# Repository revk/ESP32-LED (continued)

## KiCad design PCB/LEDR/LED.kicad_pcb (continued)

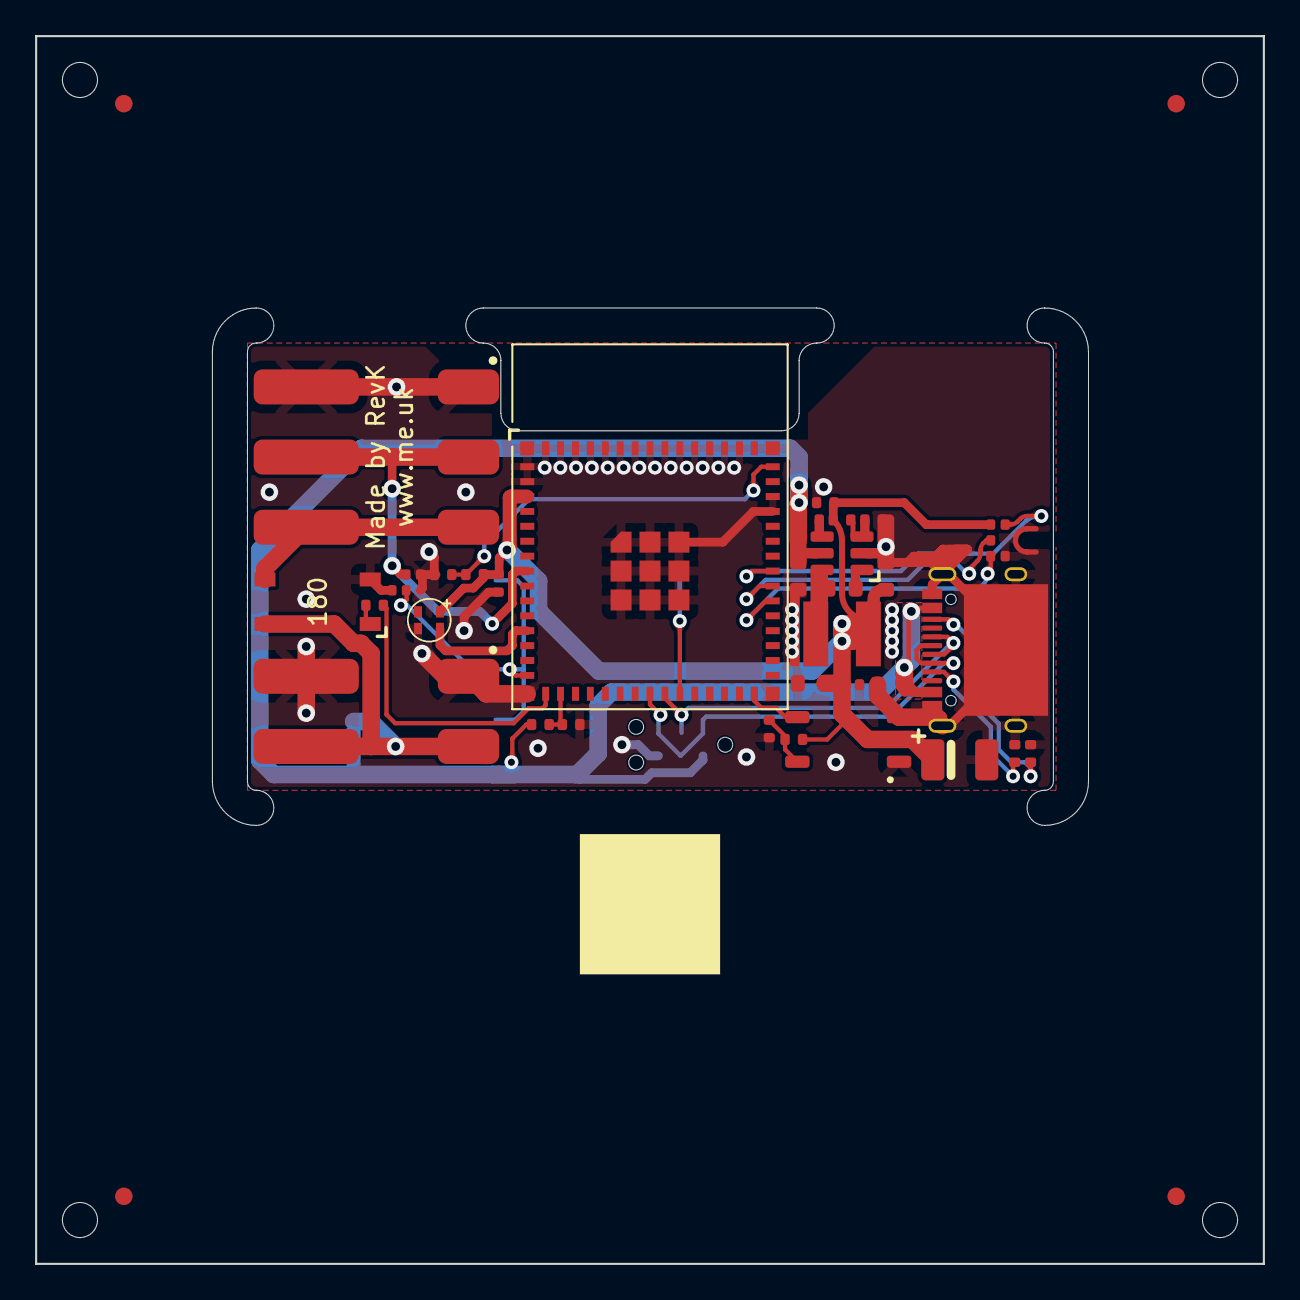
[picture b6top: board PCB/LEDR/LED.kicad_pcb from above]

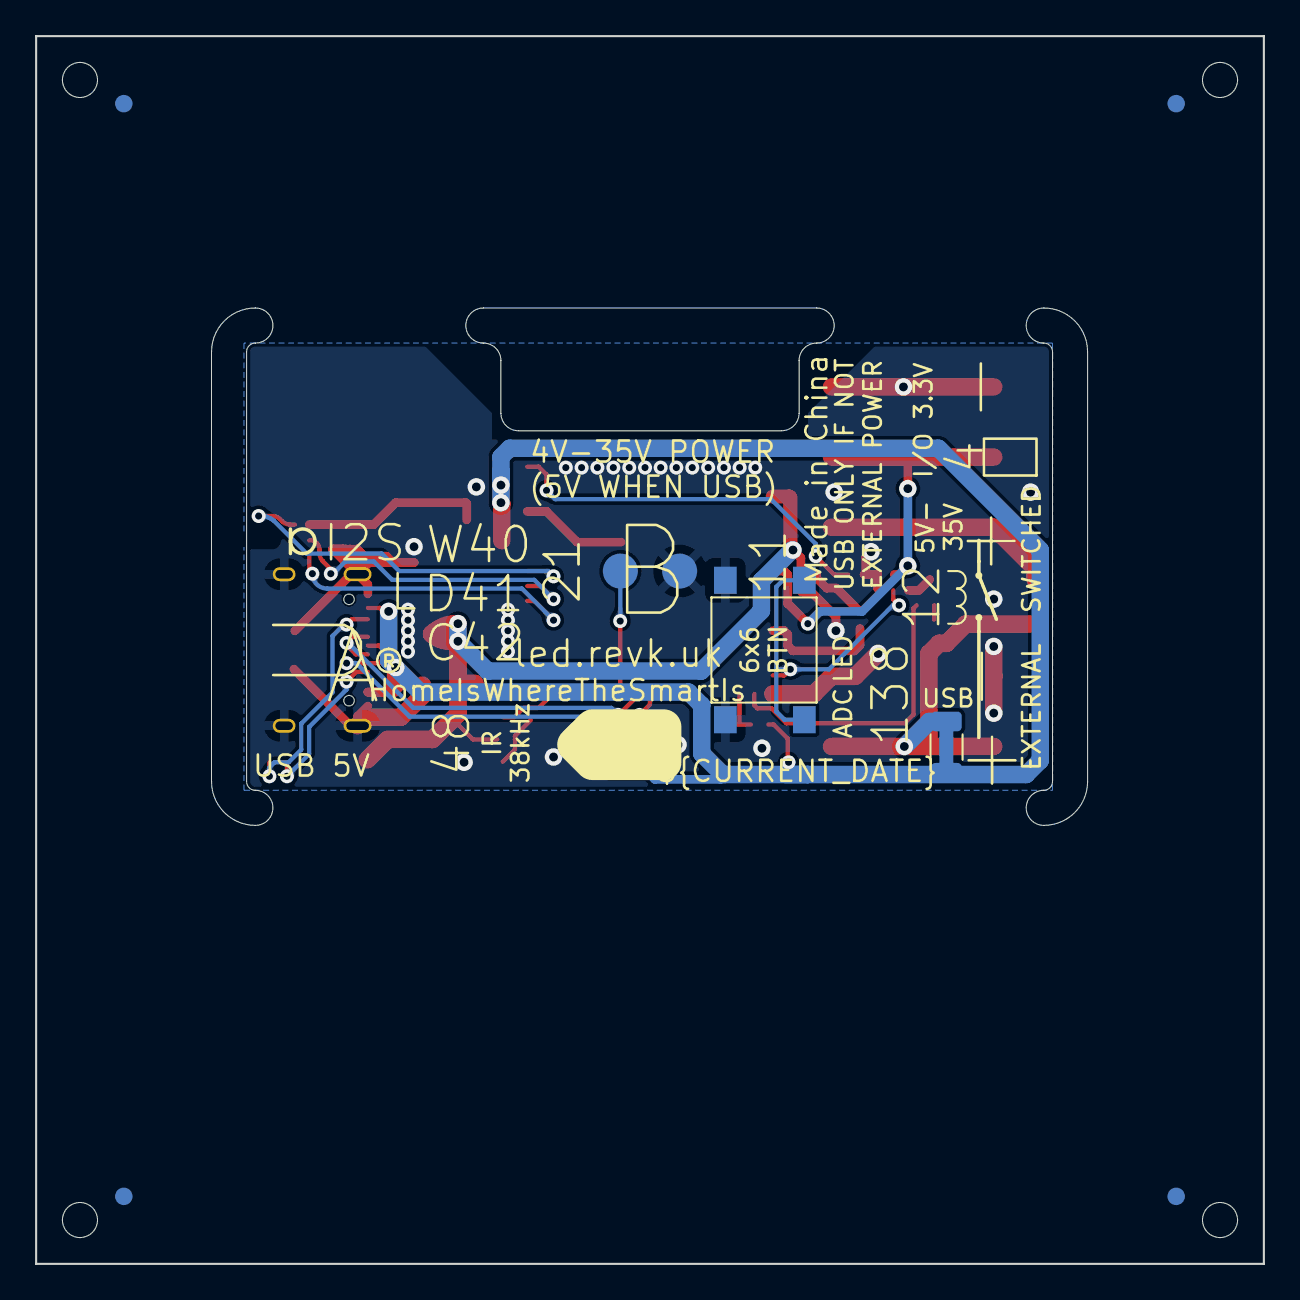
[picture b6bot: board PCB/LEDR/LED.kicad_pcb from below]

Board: 2 copper layers, 70.0 x 70.0 mm, 40 parts (4 on the bottom side), 22 nets.

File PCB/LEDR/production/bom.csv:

Designator,Footprint,Quantity,Value,LCSC Part #
C1,CP_EIA-3528-21_Kemet-B,1,220uF Tant,C122649
C10,C_0603_,1,10uF 35V,C194427
C11,C_0603_,1,10uF 6.3V,C1691
C12,C_0603_,1,100nF,
C2,C_0402,1,100nF,
C3,C_0603,1,22uF,
C4,C_0402,1,4.7uF,C194427
C5,C_0603,1,10uF 35V,C194427
"C7, C8",C_0402,2,10uF,C15525
C9,C_0402,1,1uF,
D1,SMD1615,1,XL-1010RGBC-WS2812B,C5349954
"D2, D3",DFN1006-2L,2,~,C5137770
J2,WAGO-2060-453-998-404,1,LED,C2765056
J5,USB-C-Socket-H,1,USB-C-Socket-H,C709357
J6,WAGO-2060-452-998-404,1,Power,C2765055
L2,L_4x4_,1,10uH,
R1,R_0402,1,124K,
R14,R_0402_,1,39k2,
R15,R_0402_,1,1M,
"R2, R3",R_0402,2,10K,
R4,R_0402_,1,124k,
"R5, R6",R_0402,2,5K1,
R7,R_0402,1,1K,
R9,R_0402,1,100R,
U1,ICS43434_MEMS_Mic_Open,1,ICS43434_MEMS_Mic,C5656610
U3,SO-4_4.4x4.3mm_P2.54mm,1,Relay,C2691608
U5,"SMD-4P,4x5mm",1,IRM-H638T/TR2,C91447
U6,ESP32-S3-MINI-1,1,ESP32-S3-MINI-1,C3013941
U7,SOT-23-6-MD8942,1,MD8942,C2684786

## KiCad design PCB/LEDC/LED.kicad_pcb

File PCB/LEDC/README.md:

# LEDC

## Trademark

This is an open source project, but bear in mind you cannot sell boards or cases bearing the Andrews & Arnold Ltd name, the A&A logo, the registered trademark AJK logo, or the GS1 allocated EANs assigned to Andrews & Arnold Ltd.

## PCB Designs

These files are for use with [KiCAD](https://www.kicad.org).

- [LED](LED.kicad_pro)

## 3D

3D case designs are normally automatically created from the PCB so as to ensure correct details and placement of apertures, etc.

|Design|Bottom|Top|Combined|
|------|------|---|--------|
|LED||||

## PCB Images

---

*Auto generated README.md 2025-11-15T09:00:32*

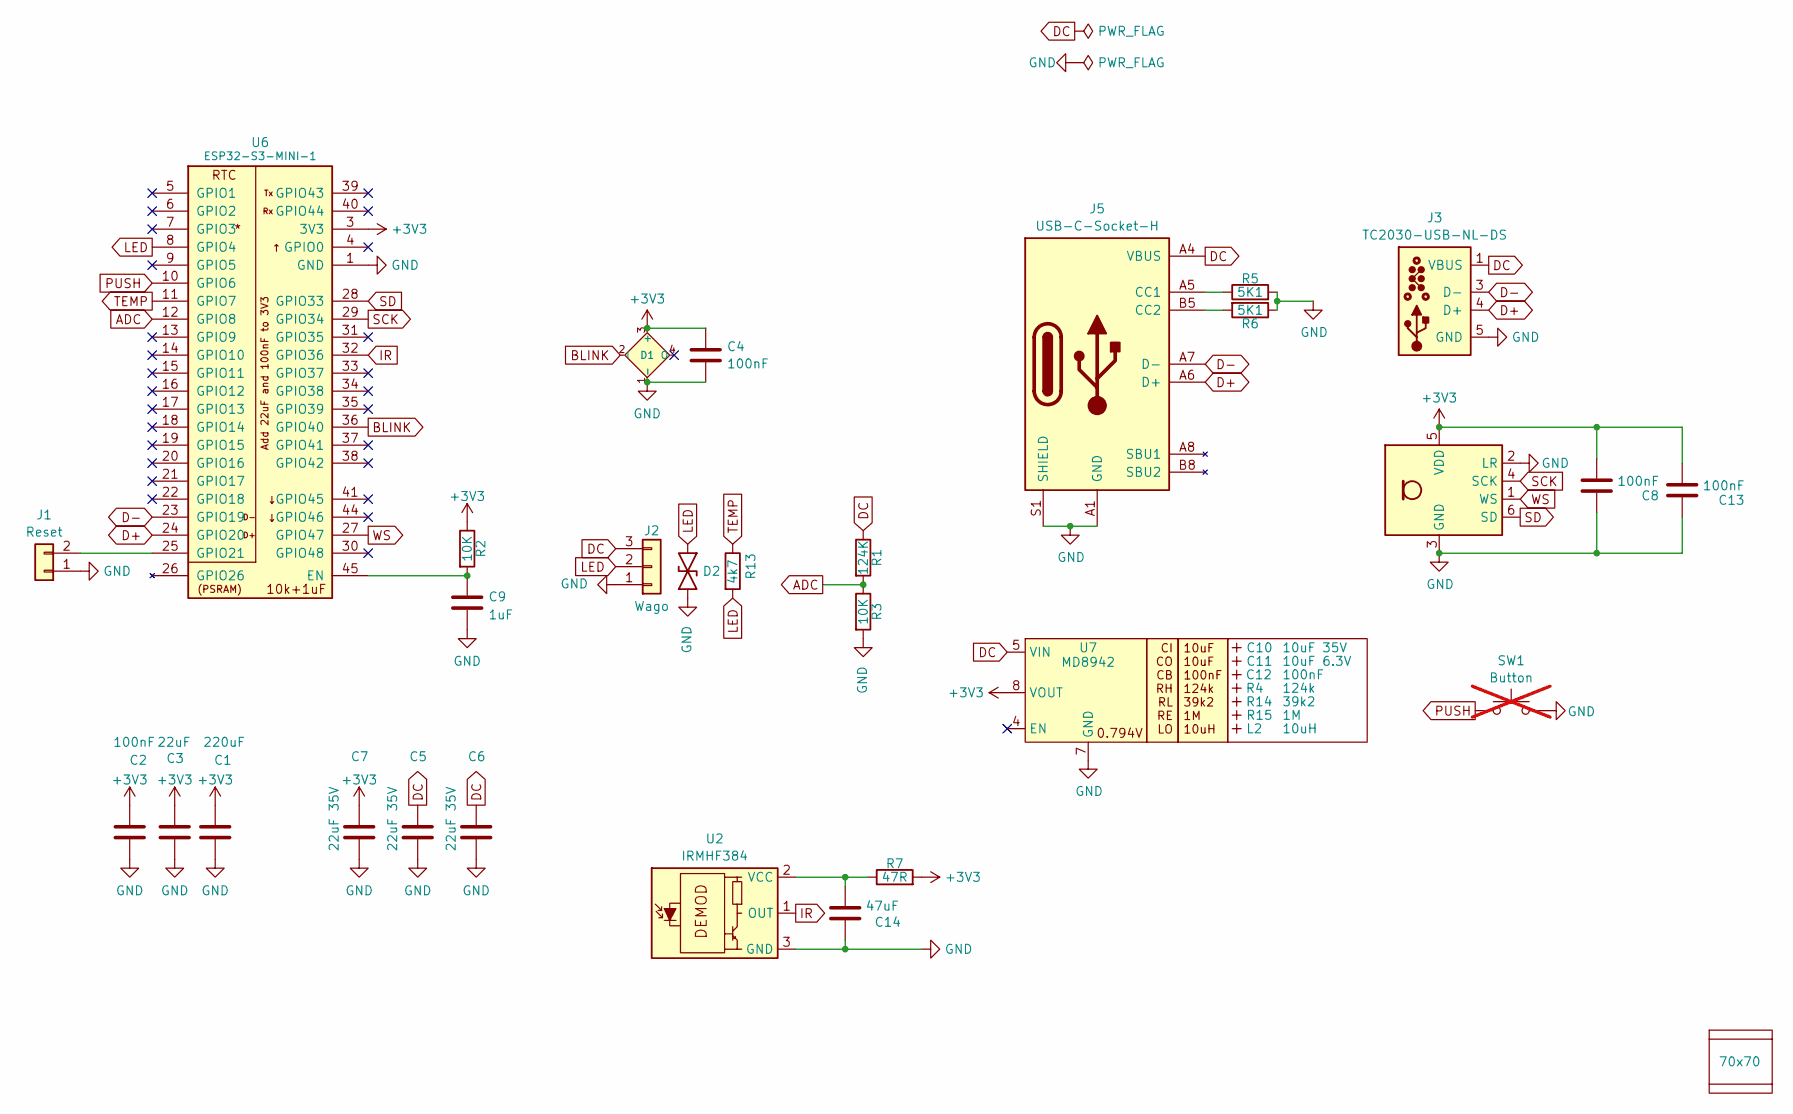
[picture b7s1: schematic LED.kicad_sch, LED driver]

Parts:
C1: 220uF; C_1206; MPN C412252
C2, C4, C8, C13: 100nF; C_0402
C3: 22uF; C_0603
C5, C6, C7: 22uF 35V; C_0805; MPN C6119901
C9: 1uF; C_0402
C10: 10uF 35V; C_0603_; MPN C194427
C11: 10uF 6.3V; C_0603_; MPN C1691
C12: 100nF; C_0603_
C14: 47uF; C_0603
D1: XL-1010RGBC-WS2812B; SMD1615; MPN C5349954
D2: DFN1006-2L; MPN C5137770
J1: Reset; AA-Pad
J2: Wago; WAGO-2060-453-998-404; MPN C2765056
J3: TC2030-USB-NL-DS; Tag-Connect_TC2030-IDC-NL_2x03_P1.27mm_Vertical
J5: USB-C-Socket-H; MPN C709357
L2: 10uH; L_4x4_; MPN C167879
PCB1: 70x70; PCB7070
R1: 124K; R_0402; MPN C2933070
R2, R3: 10K; R_0402; MPN C25744
R4: 124k; R_0402_; MPN C2933070
R5, R6: 5K1; R_0402; MPN C25905
R7: 47R; R_0402; MPN C25118
R13: 4k7; R_0402; MPN C25900
R14: 39k2; R_0402_; MPN C137996
R15: 1M; R_0402_; MPN C26083
SW1: Button; SW_Push_1P1T_NO_6x6mm; not fitted
U1: ICS43434_MEMS_Mic; ICS43434_MEMS_Mic_Open; MPN C5656610
U2: IRMHF384; IR-SMD-4P,3.35x3.9mm; MPN C7280961
U6: ESP32-S3-MINI-1; MPN C3013941
U7: MD8942; SOT-23-6-MD8942; MPN C2684786
V1, V2: VCUT70N

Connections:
+3V3: C1.1, C2.1, C3.1, C4.1, C7.1, C8.2, C13.2, D1.3 (+), R2.1, R7.2, U1.5 (VDD), U6.3 (3V3), U7.8 (VOUT)
ADC: R1.2, R3.1, U6.12 (GPIO8)
BLINK: D1.2 (I), U6.36 (GPIO40)
D+: J3.4 (D+), J5.A6 (D+), J5.B6 (D+), U6.24 (GPIO20)
D-: J3.2 (NC), J3.3 (D-), J3.6 (NC), J5.A7 (D-), J5.B7 (D-), U6.23 (GPIO19)
DC: C5.1, C6.1, J2.3, J3.1 (VBUS), J5.A4 (VBUS), J5.A9 (VBUS), J5.B4 (VBUS), J5.B9 (VBUS), R1.1, U7.5 (VIN)
GND: C1.2, C2.2, C3.2, C4.2, C5.2, C6.2, C7.2, C8.1, C9.2, C13.1, C14.2, D1.1 (-), D2.1, J1.1, J2.1, J3.5 (GND), J5.A1 (GND), J5.A12 (GND), J5.B1 (GND), J5.B12 (GND), J5.S1 (SHIELD), R3.2, R5.2, R6.1, SW1.2, U1.2 (LR), U1.3 (GND), U2.3 (GND), U2.4 (GND), U6.1 (GND), U6.2 (GND), U6.42 (GND), U6.43 (GND), U6.46 (GND), U6.47 (GND), U6.48 (GND), U6.49 (GND), U6.50 (GND), U6.51 (GND), U6.52 (GND), U6.53 (GND), U6.54 (GND), U6.55 (GND), U6.56 (GND), U6.57 (GND), U6.58 (GND), U6.59 (GND), U6.60 (GND), U6.61 (GND), U6.62 (GND), U6.63 (GND), U6.64 (GND), U6.65 (GND), U7.2 (GND), U7.7 (GND)
IR: U2.1 (OUT), U6.32 (GPIO36)
LED: D2.2, J2.2, R13.2, U6.8 (GPIO4)
unnamed: J1.2, U6.25 (GPIO21)
unnamed: J5.A5 (CC1), R5.1
unnamed: J5.B5 (CC2), R6.2
unnamed: C14.1, R7.1, U2.2 (VCC)
unnamed: C9.1, R2.2, U6.45 (EN)
PUSH: SW1.1, U6.10 (GPIO6)
SCK: U1.4 (SCK), U6.29 (GPIO34)
SD: U1.6 (SD), U6.28 (GPIO33)
TEMP: R13.1, U6.11 (GPIO7)
WS: U1.1 (WS), U6.27 (GPIO47)

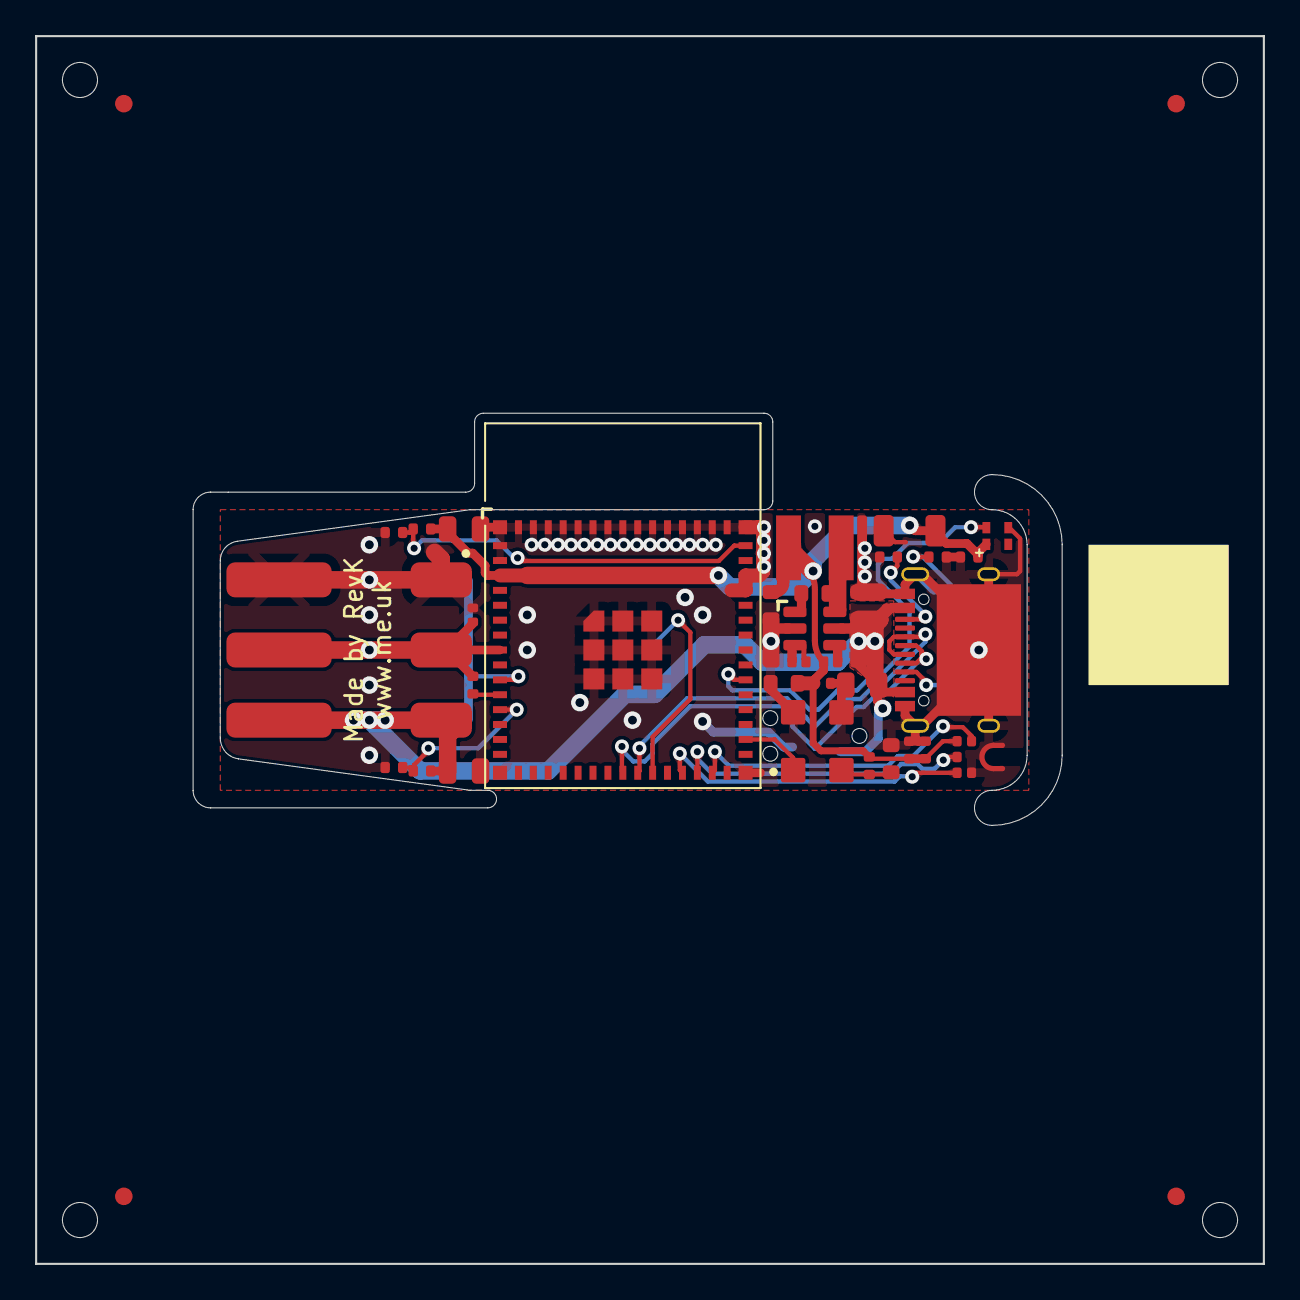
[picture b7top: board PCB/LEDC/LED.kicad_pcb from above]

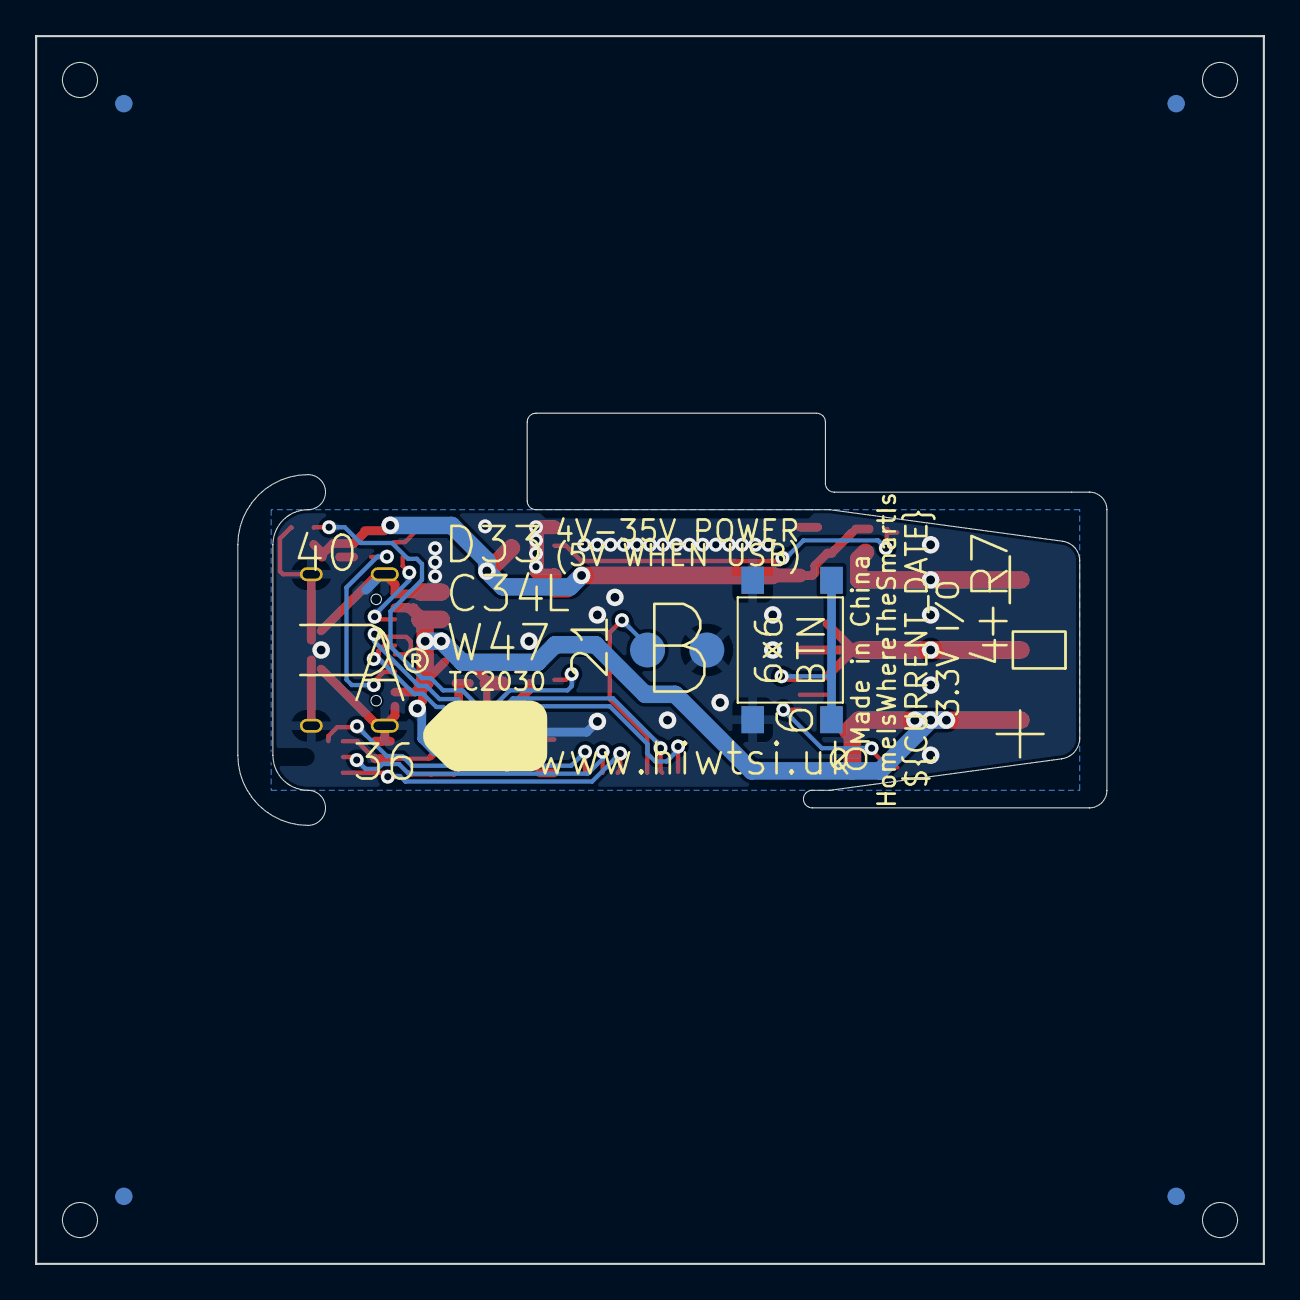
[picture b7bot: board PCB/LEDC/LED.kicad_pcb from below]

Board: 2 copper layers, 70.0 x 70.0 mm, 39 parts (3 on the bottom side), 19 nets.

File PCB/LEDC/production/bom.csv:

Designator,Footprint,Quantity,Value,LCSC Part #
C1,C_1206,1,220uF,C412252
C10,C_0603_,1,10uF 35V,C194427
C11,C_0603_,1,10uF 6.3V,C1691
C12,C_0603_,1,100nF,
"C13, C2, C4, C8",C_0402,4,100nF,
C14,C_0603,1,47uF,
C3,C_0603,1,22uF,
"C5, C6, C7",C_0805,3,22uF 35V,C6119901
C9,C_0402,1,1uF,
D1,SMD1615,1,XL-1010RGBC-WS2812B,C5349954
D2,DFN1006-2L,1,~,C5137770
J2,WAGO-2060-453-998-404,1,Wago,C2765056
J5,USB-C-Socket-H,1,USB-C-Socket-H,C709357
L2,L_4x4_,1,10uH,C167879
R1,R_0402,1,124K,C2933070
R13,R_0402,1,4k7,C25900
R14,R_0402_,1,39k2,C137996
R15,R_0402_,1,1M,C26083
"R2, R3",R_0402,2,10K,C25744
R4,R_0402_,1,124k,C2933070
"R5, R6",R_0402,2,5K1,C25905
R7,R_0402,1,47R,C25118
U1,ICS43434_MEMS_Mic_Open,1,ICS43434_MEMS_Mic,C5656610
U2,"IR-SMD-4P,3.35x3.9mm",1,IRMHF384,C7280961
U6,ESP32-S3-MINI-1,1,ESP32-S3-MINI-1,C3013941
U7,SOT-23-6-MD8942,1,MD8942,C2684786

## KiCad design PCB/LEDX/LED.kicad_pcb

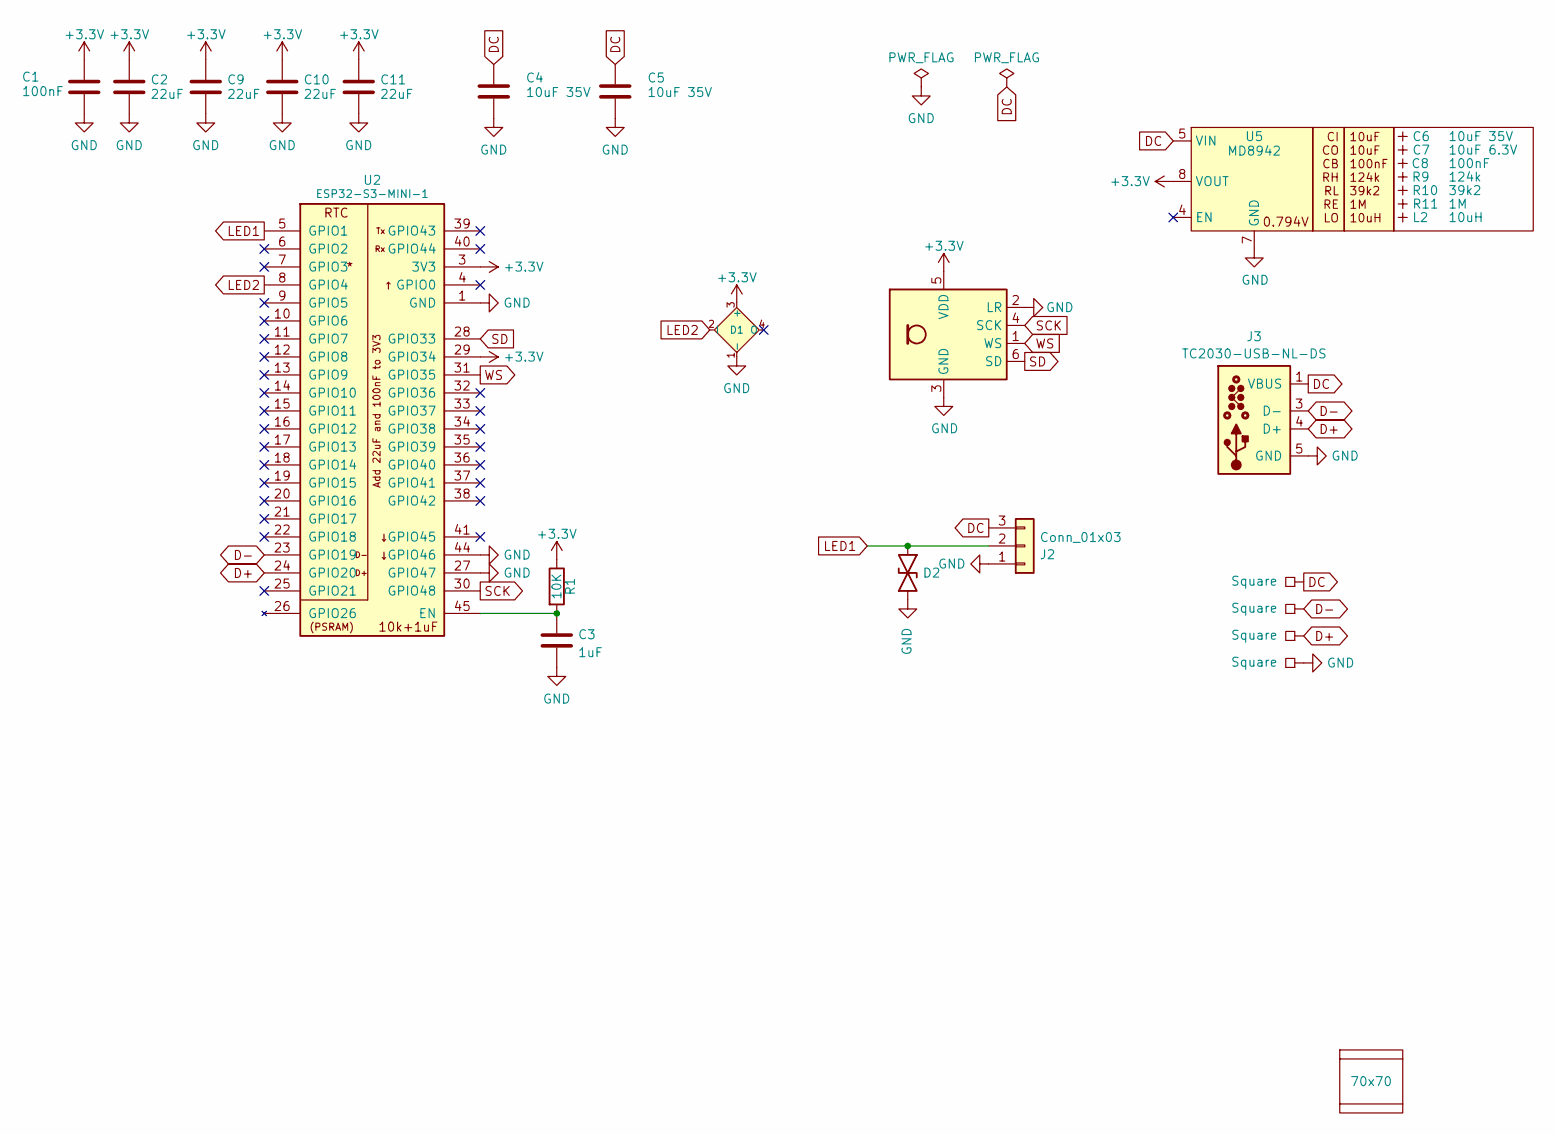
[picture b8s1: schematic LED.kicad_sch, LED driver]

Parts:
C1: 100nF; C_0402
C2, C9, C10, C11: 22uF; C_0402
C3: 1uF; C_0402
C4, C5: 10uF 35V; C_0603; MPN C194427
C6: 10uF 35V; C_0603_; MPN C194427
C7: 10uF 6.3V; C_0603_; MPN C1691
C8: 100nF; C_0603_
D1: XL-1010RGBC-WS2812B; SMD1615; MPN C5349954
D2: DFN1006-2L; MPN C5137770
J2: Conn_01x03; WAGO-2060-453-998-404-O; MPN C2765056
J3: TC2030-USB-NL-DS; Tag-Connect_TC2030-IDC-NL_2x03_P1.27mm_Vertical
L2: 10uH; L_4x4_
P1, P2, P3, P4: Square; PAD-2mm
PCB1: 70x70; PCB7070
R1: 10K; R_0402
R9: 124k; R_0402_
R10: 39k2; R_0402_
R11: 1M; R_0402_
U1: ICS43434_MEMS_Mic; MPN C5656610
U2: ESP32-S3-MINI-1; MPN C3013941
U5: MD8942; SOT-23-6-MD8942; MPN C2684786
V1, V2: 70; VCUT70N

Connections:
+3.3V: C1.1, C2.1, C9.1, C10.1, C11.1, D1.3 (+), R1.1, U1.5 (VDD), U2.3 (3V3), U2.29 (GPIO34), U5.8 (VOUT)
D+: J3.4 (D+), P3.1, U2.24 (GPIO20)
D-: J3.2 (NC), J3.3 (D-), J3.6 (NC), P2.1, U2.23 (GPIO19)
DC: C4.1, C5.1, J2.3, J3.1 (VBUS), P1.1, U5.5 (VIN)
GND: C1.2, C2.2, C3.2, C4.2, C5.2, C9.2, C10.2, C11.2, D1.1 (-), D2.1, J2.1, J3.5 (GND), P4.1, U1.2 (LR), U1.3 (GND), U2.1 (GND), U2.2 (GND), U2.27 (GPIO47), U2.42 (GND), U2.43 (GND), U2.44 (GPIO46), U2.46 (GND), U2.47 (GND), U2.48 (GND), U2.49 (GND), U2.50 (GND), U2.51 (GND), U2.52 (GND), U2.53 (GND), U2.54 (GND), U2.55 (GND), U2.56 (GND), U2.57 (GND), U2.58 (GND), U2.59 (GND), U2.60 (GND), U2.61 (GND), U2.62 (GND), U2.63 (GND), U2.64 (GND), U2.65 (GND), U5.2 (GND), U5.7 (GND)
LED1: D2.2, J2.2, U2.5 (GPIO1)
LED2: D1.2 (I), U2.8 (GPIO4)
unnamed: C3.1, R1.2, U2.45 (EN)
SCK: U1.4 (SCK), U2.30 (GPIO48)
SD: U1.6 (SD), U2.28 (GPIO33)
WS: U1.1 (WS), U2.31 (GPIO35)

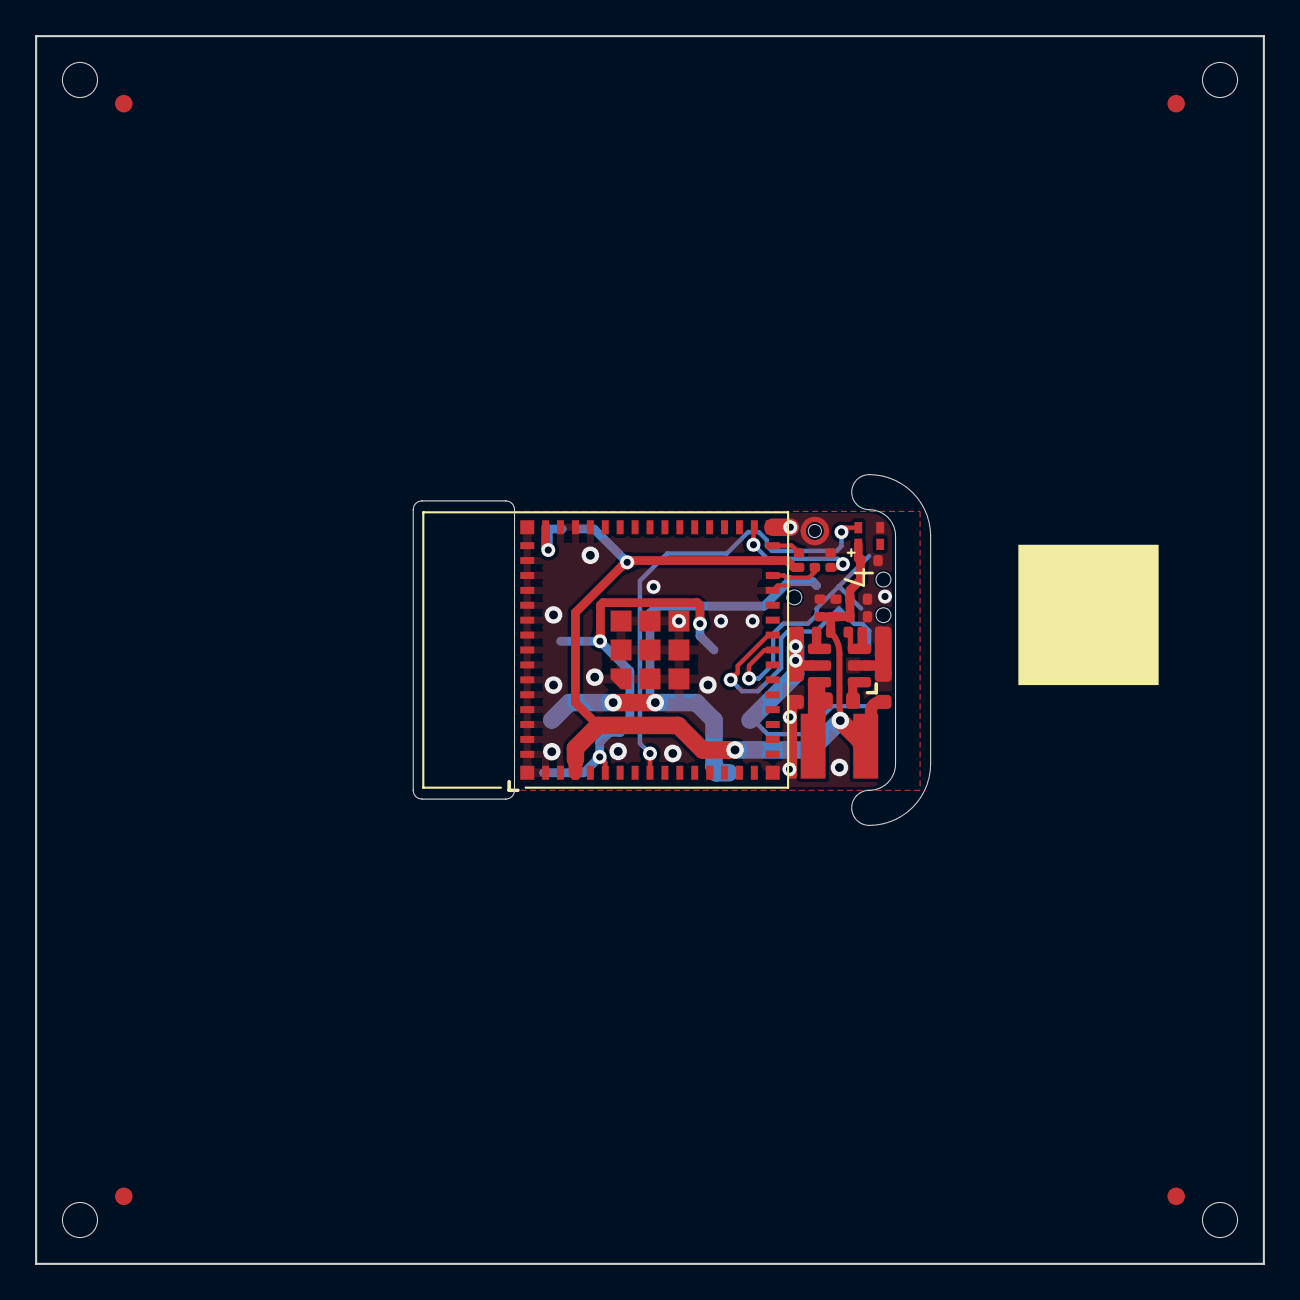
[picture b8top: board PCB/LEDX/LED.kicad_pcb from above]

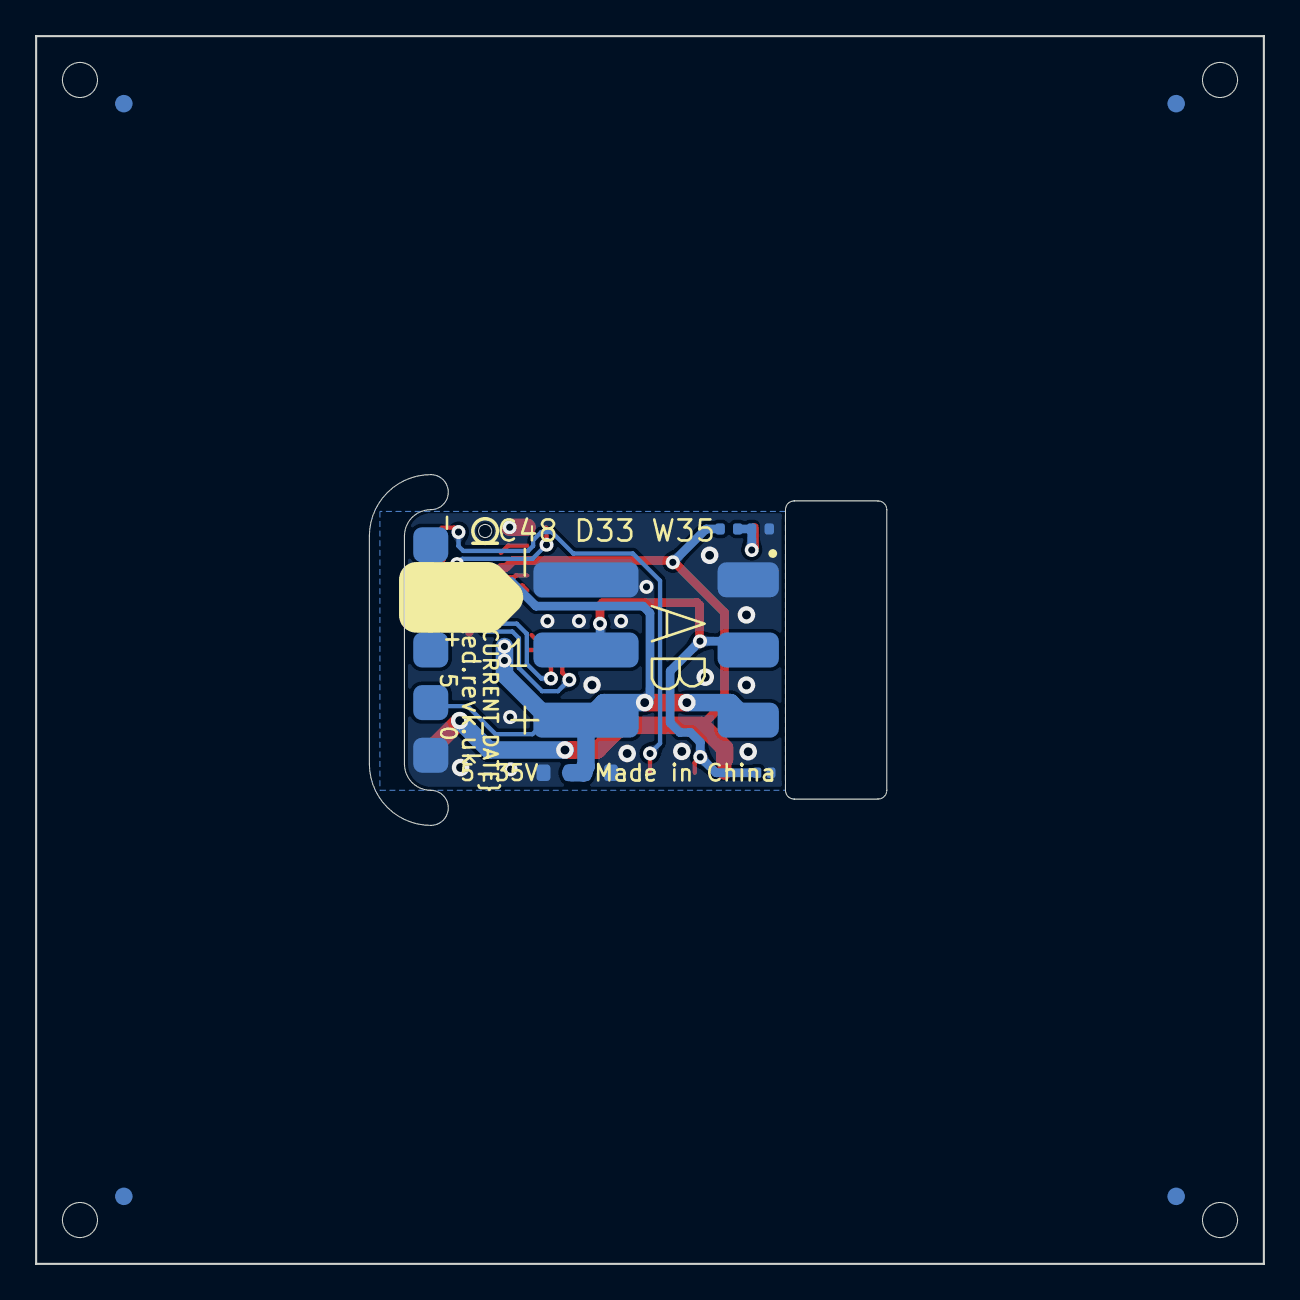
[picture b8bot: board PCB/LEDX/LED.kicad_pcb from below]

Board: 2 copper layers, 70.0 x 70.0 mm, 30 parts (13 on the bottom side), 11 nets.

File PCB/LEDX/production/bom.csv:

Designator,Footprint,Quantity,Value,LCSC Part #
C1,C_0402,1,100nF,
"C10, C11, C2, C9",C_0402,4,22uF,
C3,C_0402,1,1uF,
"C4, C5",C_0603,2,10uF 35V,C194427
C6,C_0603_,1,10uF 35V,C194427
C7,C_0603_,1,10uF 6.3V,C1691
C8,C_0603_,1,100nF,
D1,SMD1010,1,XL-1010RGBC-WS2812B,C5349953
D2,DFN1006-2L,1,~,C5137770
J2,WAGO-2060-453-998-404-O,1,Conn_01x03,C2765056
L2,L_4x4_,1,10uH,
R1,R_0402,1,10K,
R10,R_0402_,1,39k2,
R11,R_0402_,1,1M,
R9,R_0402_,1,124k,
U1,ICS43434_MEMS_Mic,1,ICS43434_MEMS_Mic,C5656610
U2,ESP32-S3-MINI-1,1,ESP32-S3-MINI-1,C3013941
U5,SOT-23-6-MD8942,1,MD8942,C2684786

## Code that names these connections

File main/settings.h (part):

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#else
extern uint8_t cps;	// Change per second
#endif
extern revk_gpio_t relay;	// Relay for strip power
extern revk_gpio_t adc;	// ADC*13.4
extern revk_gpio_t button;	// Button
extern revk_gpio_t irgpio;	// IR receiver
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#define	ir4x6	revk_settings_bits.ir4x6
#define	irha	revk_settings_bits.irha
#ifdef  CONFIG_REVK_LED_TEST
extern revk_gpio_t blink[3];	// R, G, B LED array (for WS2818, set first two the same, third can be loop test)
#else
extern revk_gpio_t blink[3];	// R, G, B LED array (for WS2812, set first two the same)
#endif
extern uint8_t maxr;	// Max RGB Red
extern uint8_t maxg;	// Max RGB Green
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extern uint8_t lsals;	// Colour sensor ID
extern revk_gpio_t micdata;	// I2S Mic Data / SD / DATA
extern revk_gpio_t micclock;	// I2S Mic Clock / BCLK / SCK
extern revk_gpio_t micws;	// I2S Mic WS / LR (not set for PDM mode)
#define	micright	revk_settings_bits.micright
extern uint8_t micdamp;	// I2S Mic Damping from peak (higher is slower)
extern uint8_t micmaxgain;	// Max mic gain
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#define	prefixhost	revk_settings_bits.prefixhost
#ifdef	CONFIG_REVK_BLINK_DEF
#ifdef	CONFIG_REVK_BLINK_WS2812_DEF
extern revk_gpio_t blink;	// WS2812 LED
#ifdef	CONFIG_REVK_LED_TEST
extern revk_gpio_t blinktest;	// WS2812 LED loopback for testing LED strip
#endif
#define	ws2812rgb	revk_settings_bits.ws2812rgb
#else
#ifdef	CONFIG_REVK_LED_TEST
extern revk_gpio_t blink[3];	// R, G, B LED array (for WS2818, set first two the same, third can be loop test)
#else
extern revk_gpio_t blink[3];	// R, G, B LED array (for WS2812, set first two the same)
#endif
#endif
#endif
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
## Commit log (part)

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2025-01-14 Cleaner restart
2025-01-14 release/beta
2025-01-14 Tidy on/off
2025-01-14 Crash
2025-01-15 Control which effect on power and clap
2025-01-15 Button and fixes
2025-01-15 Tidy
2025-01-15 Fix bugs
2025-01-15 Try that
2025-01-15 Makefile tweak
2025-01-15 Release
2025-01-15 No point as issue always from Linux anyway
2025-01-16 LED35 added
2025-01-16 Ok 32mm
2025-01-18 Library update
2025-01-18 Re-image
2025-01-18 Tidy images
2025-01-18 Tidy parts
2025-01-18 Various typo fixes, minor language changes for clarity
2025-01-18 No LDO
2025-01-18 Dimensions
2025-01-18 Improved help text
2025-01-18 Image
2025-01-18 More images
2025-01-19 Cleaner logic
2025-01-19 Restart fix
2025-01-21 Colour
2025-01-21 Coaster
2025-01-21 Re render (colours)
2025-01-22 New LED types
2025-01-22 New type
2025-01-22 Wording
2025-01-23 PCB Update
2025-01-24 Images
2025-01-25 Only 4 RMT total, so 3 LED strips
2025-01-25 New README
2025-01-25 Update README.md
    All images
2025-01-25 Latest layout
2025-01-26 Report when goes off
2025-01-30 Datamatrix
2025-02-02 USB uptime
2025-02-02 usbuptime
2025-02-04 Fixed render
2025-02-05 Render
2025-02-10 More caps
2025-02-21 PCB tidy
2025-04-04 Default current build if not bin file
2025-04-04 Changed GPIO
2025-04-28 Larger caps
2025-04-28 Bigger caps
2025-05-24 WAGO power pads
2025-05-24 s/w and WLED link
2025-05-24 Note on software
2025-06-01 New design
2025-06-08 Start on IR
2025-06-08 Start IR
2025-06-08 Added IR remote controls
2025-06-08 DIYn
2025-06-10 Tweak
2025-06-22 New power control on LEDC
2025-06-22 Revert as too high voltage for part
2025-06-27 4k7 for DS18B20?
2025-07-12 12V version
2025-07-19 Updated STL
2025-07-19 rerender/case
2025-07-19 Updated IR
2025-08-04 Case update
2025-08-12 Re-do cases
2025-08-15 scale
2025-08-15 Margins tidy
2025-08-15 Re render
2025-08-24 Remaker
2025-08-24 Render and date code
2025-08-25 Re render case# Please enter the commit message for your changes. Lines starting
2025-08-26 new cases
2025-08-29 As ordered today
2025-08-30 Thicker wall
2025-09-04 Slight change
2025-09-07 New coaster case
2025-09-07 New case
2025-09-07 Case design
2025-09-07 thicker
2025-09-07 More base bumps
2025-09-07 Case tidy
2025-09-08 Clean up
2025-09-08 PCB based values
2025-09-11 Cleaner
2025-09-18 Slight changes
2025-09-21 New LEDX12
2025-09-21 Updated (thicker case)
2025-09-21 As ordered
2025-09-24 Revised
2025-09-24 rerender
2025-09-29 Test boards
2025-09-30 Manifest
2025-09-30 Change default GPIO
2025-09-30 LEDX12 manifest/NVS
2025-09-30 Spacing
2025-09-30 Latest
2025-10-01 Tweaked design
2025-10-01 Fix GPIO label
2025-10-01 Re-render
2025-10-03 New ATE logic
2025-10-04 LEDC12
2025-10-04 Started on WLED
2025-10-05 ATE update
2025-10-05 WLED manifest
2025-10-05 WLED
2025-10-06 Ready for LEDX12-WLED
2025-10-06 Code last
2025-10-09 New LEDs
2025-10-09 Started Coaster3 for new LEDs
2025-10-10 New coaster
2025-10-10 Bigger hole
2025-10-15 Update test seven seg
2025-10-15 Tweak board
2025-10-25 Timed presets
2025-10-26 New test pattern logic
2025-10-26 RGB/RGBW for test
2025-10-26 WLED message before config
2025-10-27 test allows fixed colour at end
2025-10-29 GPIO 1
2025-10-29 FFS²
2025-10-29 FFS³
2025-11-01 RTe-render
2025-11-05 Cleaner render
2025-11-07 speed on text
2025-11-07 Speed 2 places
2025-11-07 try larger types
2025-11-07 Revert speed changes
2025-11-07 Revert
2025-11-08 More
2025-11-09 README
2025-11-13 New OTA
2025-11-13 New lib
2025-11-13 Beta
2025-11-15 Not a good case, but started one, and some cleaner renders
2025-11-19 fix: Text scrolling Added speed control to scrolling text (seconds per character) Added snake and flip and height as globals for text Extended clock to seconds if space
2025-11-19 Edge case on offset text
2025-11-20 fix: Clock - change kerning and zero to be fixed space and neater
2025-11-20 fix: scrolling kerned text
2025-11-20 fix: character height squashing (good at 7 and 8, less so at lower values)
2025-11-20 Non gamma option (currently global)
2025-11-23 Right margin
2025-11-23 Cleaner gradient
2026-01-04 Simplifed
2026-01-05 Attempt at long strings - not quite there yet
2026-01-15 No BLE
2026-01-18 Minor tweaks, websockets being ofd on IPv6 from safari for some reason
